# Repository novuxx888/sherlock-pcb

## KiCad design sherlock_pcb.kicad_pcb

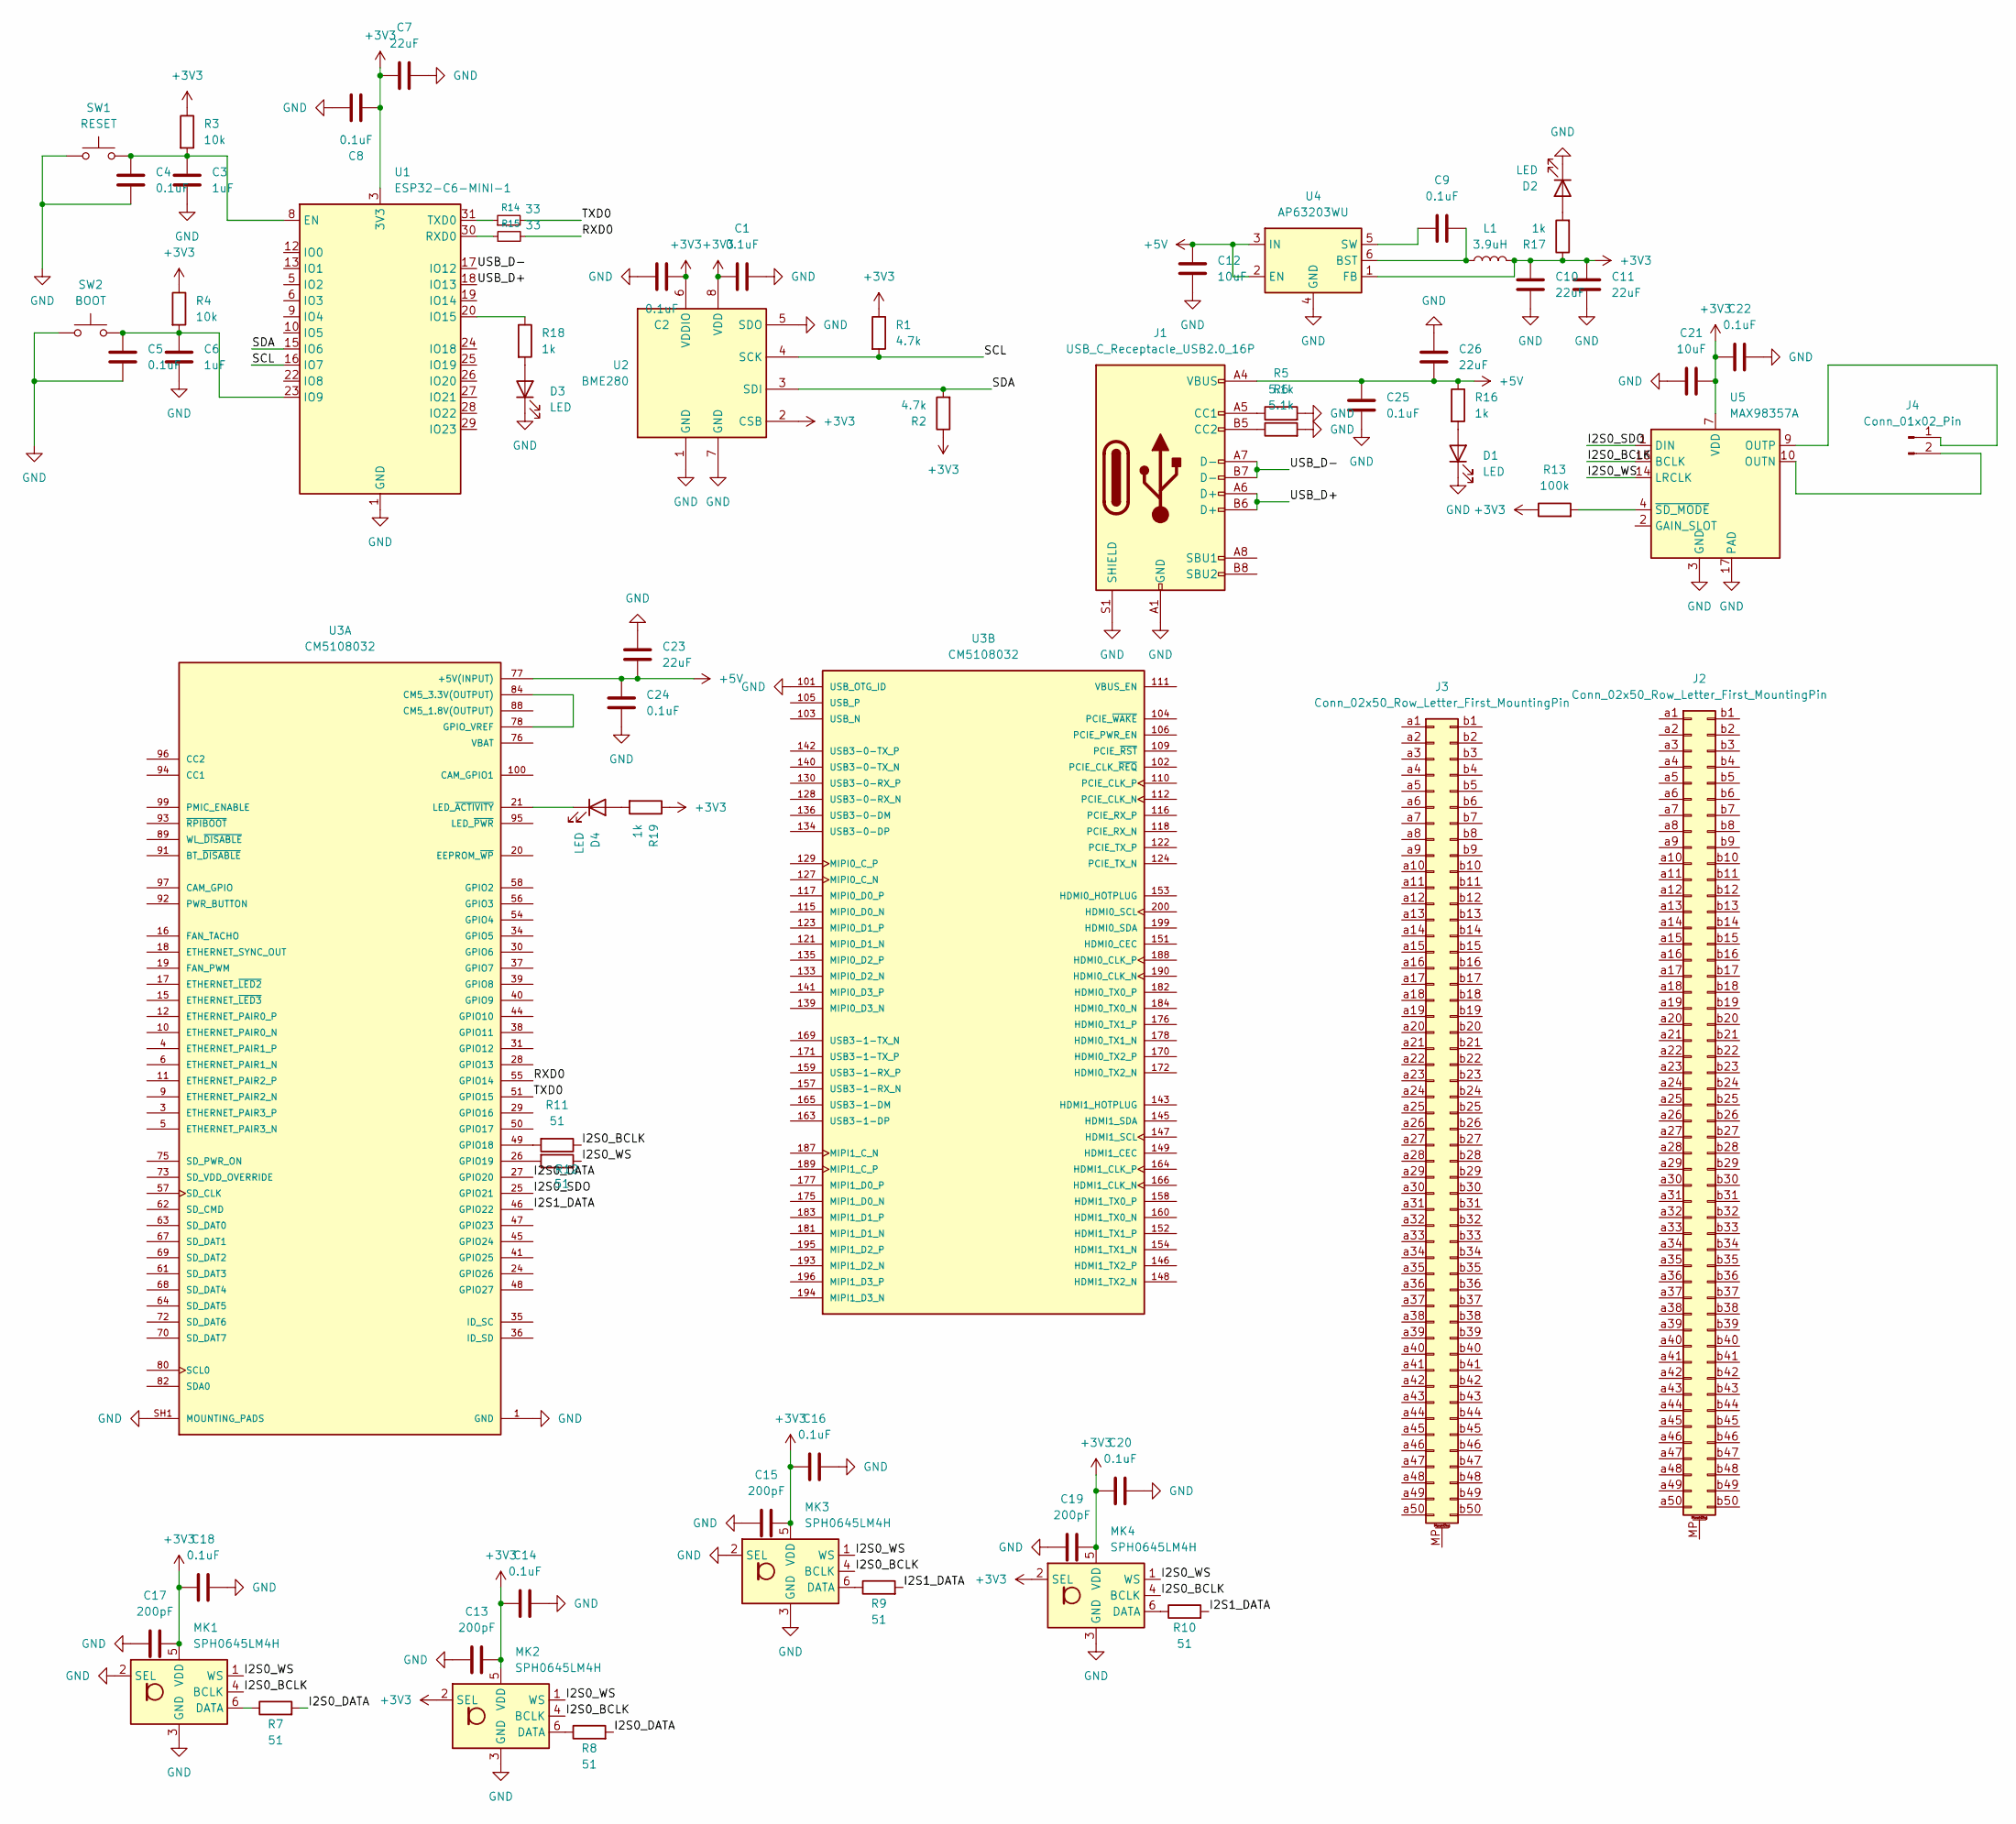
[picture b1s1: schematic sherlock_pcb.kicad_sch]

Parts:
C1, C2, C4, C5, C8, C9, C14, C16, C18, C20, C22, C24, C25: 0.1uF; C_0402_1005Metric; LCSC C1525
C3, C6: 1uF; C_0402_1005Metric; LCSC C52923
C7, C10, C11, C23, C26: 22uF; C_0603_1608Metric; LCSC C59461
C12, C21: 10uF; C_0603_1608Metric; LCSC C1691
C13, C15, C17, C19: 200pF; C_0402_1005Metric; LCSC C1529
D1, D2, D3, D4: LED; LED_0603_1608Metric; LCSC C2290
J1: USB_C_Receptacle_USB2.0_16P; USB_C_Receptacle_GCT_USB4105-xx-A_16P_TopMnt_Horizontal; LCSC C165948
J2, J3: Conn_02x50_Row_Letter_First_MountingPin; Hirose_DF40C-100DS-0.4V_2x50_P0.4mm; LCSC C597931
J4: Conn_01x02_Pin; Molex_PicoBlade_53261-0271_1x02-1MP_P1.25mm_Horizontal; LCSC C22074
L1: 3.9uH; L_1008_2520Metric; LCSC C250157
MK1, MK2, MK3, MK4: SPH0645LM4H; Knowles_SPH0645LM4H-6_3.5x2.65mm; LCSC C19272537
R1, R2: 4.7k; R_0402_1005Metric; LCSC C25900
R3, R4: 10k; R_0402_1005Metric; LCSC C25531
R5, R6: 5.1k; R_0402_1005Metric; LCSC C25905
R7, R8, R9, R10, R11, R12: 51; R_0402_1005Metric; LCSC C25125
R13: 100k; R_0402_1005Metric; LCSC C25530
R14, R15: 33; R_0402_1005Metric; LCSC C25105
R16, R17, R18, R19: 1k; R_0402_1005Metric; LCSC C11702
SW1: RESET; SW_SPST_PTS810; LCSC C221895
SW2: BOOT; SW_SPST_PTS810; LCSC C221895
U1: ESP32-C6-MINI-1; LCSC C5736265
U2: BME280; Bosch_LGA-8_2.5x2.5mm_P0.65mm_ClockwisePinNumbering; LCSC C92489
U3: CM5108032; MODULE_CM5108032; PARTREV 2024-11-27
U4: AP63203WU; TSOT-23-6; LCSC C2071056
U5: MAX98357A; TQFN-16-1EP_3x3mm_P0.5mm_EP1.23x1.23mm; LCSC C2682619

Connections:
+3V3: C1.1, C2.1, C7.2, C8.1, C10.2, C11.2, C13.2, C14.1, C15.2, C16.1, C17.2, C18.1, C19.2, C20.1, C21.1, C22.2, L1.2, MK1.5 (VDD), MK2.2 (SEL), MK2.5 (VDD), MK3.5 (VDD), MK4.2 (SEL), MK4.5 (VDD), R1.1, R2.1, R3.1, R4.1, R13.1, R17.1, R19.1, U1.3 (3V3), U2.2 (CSB), U2.6 (VDDIO), U2.8 (VDD), U4.1 (FB), U5.7 (VDD), U5.8 (VDD)
+5V: C12.2, C23.2, C24.2, C25.2, C26.2, J1.A4 (VBUS), J1.A9 (VBUS), J1.B4 (VBUS), J1.B9 (VBUS), R16.1, U3.77 (+5V(INPUT)), U3.79 (+5V(INPUT)), U3.81 (+5V(INPUT)), U3.83 (+5V(INPUT)), U3.85 (+5V(INPUT)), U3.87 (+5V(INPUT)), U4.2 (EN), U4.3 (IN)
/I2S0_BCLK: MK1.4 (BCLK), MK2.4 (BCLK), MK3.4 (BCLK), MK4.4 (BCLK), R11.1, U5.16 (BCLK)
/I2S0_DATA: R7.2, R8.2, U3.27 (GPIO20)
/I2S0_SDO: U3.25 (GPIO21), U5.1 (DIN)
/I2S0_WS: MK1.1 (WS), MK2.1 (WS), MK3.1 (WS), MK4.1 (WS), R12.1, U5.14 (LRCLK)
/I2S1_DATA: R9.2, R10.2, U3.46 (GPIO22)
/RXD0: R15.2, U3.55 (GPIO14)
/SCL: R1.2, U1.16 (IO7), U2.4 (SCK)
/SDA: R2.2, U1.15 (IO6), U2.3 (SDI)
/TXD0: R14.2, U3.51 (GPIO15)
/USB_D+: J1.A6 (D+), J1.B6 (D+), U1.18 (IO13)
/USB_D-: J1.A7 (D-), J1.B7 (D-), U1.17 (IO12)
CM5_1.8V(OUTPUT): U3.88 (CM5_1.8V(OUTPUT)), U3.90 (CM5_1.8V(OUTPUT))
CM5_3.3V(OUTPUT): U3.78 (GPIO_VREF), U3.84 (CM5_3.3V(OUTPUT)), U3.86 (CM5_3.3V(OUTPUT))
GND: C1.2, C2.2, C3.2, C4.2, C5.2, C6.2, C7.1, C8.2, C10.1, C11.1, C12.1, C13.1, C14.2, C15.1, C16.2, C17.1, C18.2, C19.1, C20.2, C21.2, C22.1, C23.1, C24.1, C25.1, C26.1, D1.1 (K), D2.1 (K), D3.1 (K), J1.A1 (GND), J1.A12 (GND), J1.B1 (GND), J1.B12 (GND), J1.S1 (SHIELD), MK1.2 (SEL), MK1.3 (GND), MK2.3 (GND), MK3.2 (SEL), MK3.3 (GND), MK4.3 (GND), R5.2, R6.2, SW1.1, SW2.1, U1.1 (GND), U1.2 (GND), U1.11 (GND), U1.14 (GND), U1.36 (GND), U1.37 (GND), U1.38 (GND), U1.39 (GND), U1.40 (GND), U1.41 (GND), U1.42 (GND), U1.43 (GND), U1.44 (GND), U1.45 (GND), U1.46 (GND), U1.47 (GND), U1.48 (GND), U1.49 (GND), U1.50 (GND), U1.51 (GND), U1.52 (GND), U1.53 (GND), U2.1 (GND), U2.5 (SDO), U2.7 (GND), U3.1 (GND), U3.2 (GND), U3.7 (GND), U3.8 (GND), U3.13 (GND), U3.14 (GND), U3.22 (GND), U3.23 (GND), U3.32 (GND), U3.33 (GND), U3.42 (GND), U3.43 (GND), U3.52 (GND), U3.53 (GND), U3.59 (GND), U3.60 (GND), U3.65 (GND), U3.66 (GND), U3.71 (GND), U3.74 (GND), U3.98 (GND), U3.101 (USB_OTG_ID), U3.107 (GND), U3.108 (GND), U3.113 (GND), U3.114 (GND), U3.119 (GND), U3.120 (GND), U3.125 (GND), U3.126 (GND), U3.131 (GND), U3.132 (GND), U3.137 (GND), U3.138 (GND), U3.144 (GND), U3.150 (GND), U3.155 (GND), U3.156 (GND), U3.161 (GND), U3.162 (GND), U3.167 (GND), U3.168 (GND), U3.173 (GND), U3.174 (GND), U3.179 (GND), U3.180 (GND), U3.185 (GND), U3.186 (GND), U3.191 (GND), U3.192 (GND), U3.197 (GND), U3.198 (GND), U3.SH1 (MOUNTING_PADS), U3.SH2 (MOUNTING_PADS), U3.SH3 (MOUNTING_PADS), U3.SH4 (MOUNTING_PADS), U4.4 (GND), U5.3 (GND), U5.11 (GND), U5.15 (GND), U5.17 (PAD)
unnamed: D1.2 (A), R16.2
unnamed: D2.2 (A), R17.2
unnamed: D3.2 (A), R18.2
unnamed: D4.2 (A), R19.2
unnamed: D4.1 (K), U3.21 (LED_~ACTIVITY)
unnamed: J1.A5 (CC1), R5.1
unnamed: J1.B5 (CC2), R6.1
unnamed: J4.1, U5.9 (OUTP)
unnamed: J4.2, U5.10 (OUTN)
unnamed: MK1.6 (DATA), R7.1
unnamed: MK2.6 (DATA), R8.1
unnamed: MK3.6 (DATA), R9.1
unnamed: MK4.6 (DATA), R10.1
unnamed: C3.1, C4.1, R3.2, SW1.2, U1.8 (EN)
unnamed: C5.1, C6.1, R4.2, SW2.2, U1.23 (IO9)
unnamed: R18.1, U1.20 (IO15)
unnamed: R15.1, U1.30 (RXD0)
unnamed: R14.1, U1.31 (TXD0)
unnamed: R11.2, U3.49 (GPIO18)
unnamed: R12.2, U3.26 (GPIO19)
unnamed: C9.2, L1.1, U4.6 (BST)
unnamed: C9.1, U4.5 (SW)
unnamed: R13.2, U5.4 (~SD_MODE)

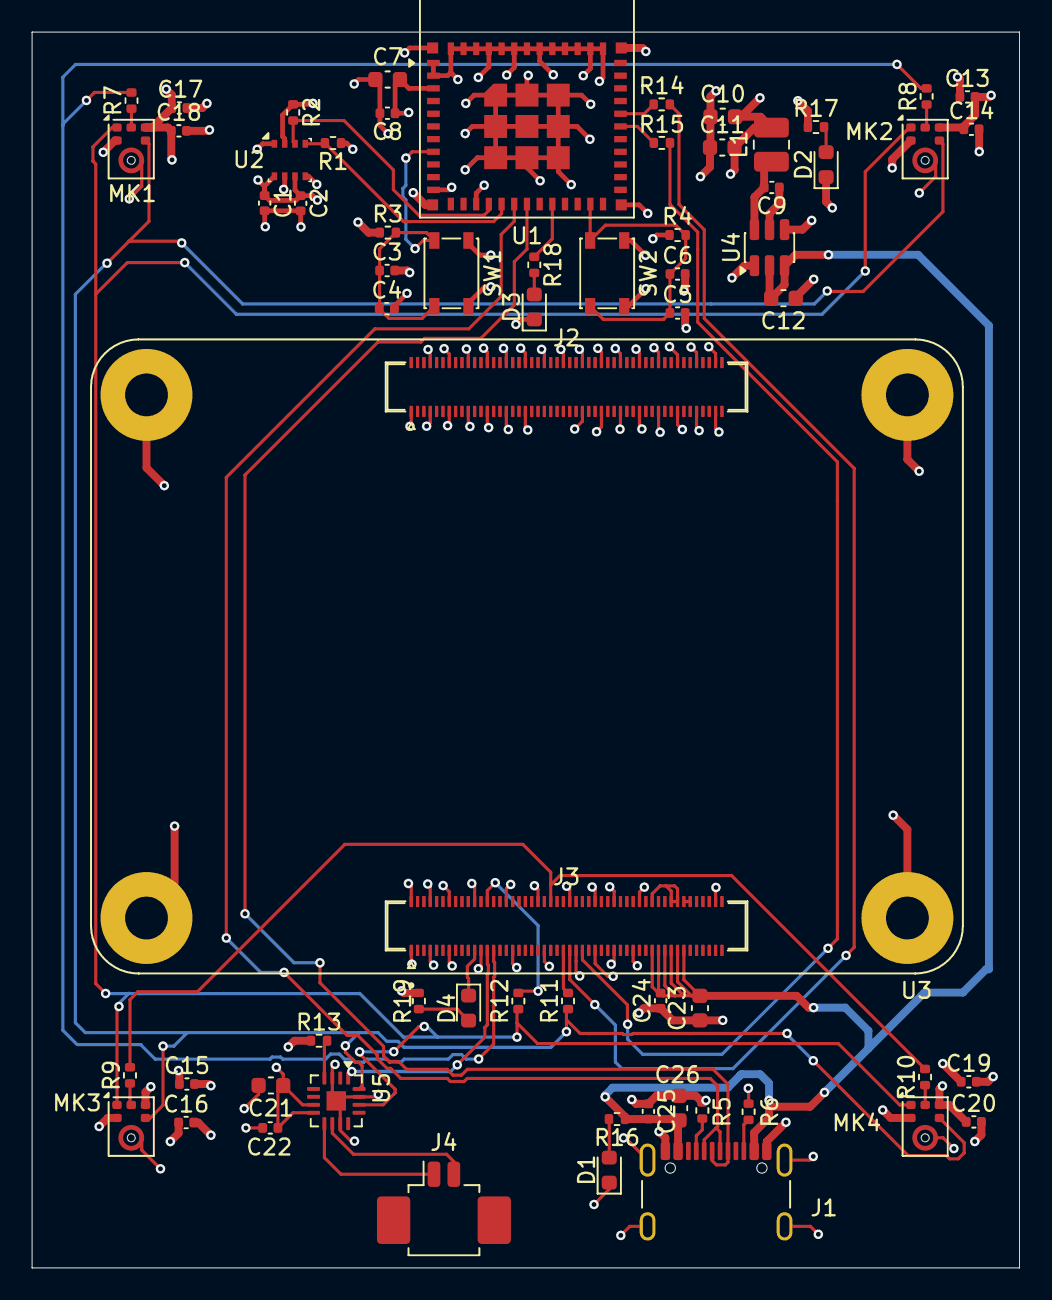
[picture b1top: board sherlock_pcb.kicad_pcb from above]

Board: 4 copper layers, 62.3 x 78.0 mm, 65 parts (0 on the bottom side), 39 nets.

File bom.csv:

Designator,Footprint,Quantity,Value,LCSC Part #
"C1, C14, C16, C18, C2, C20, C22, C24, C25, C4, C5, C8, C9",0402,13,0.1uF,C1525
"C10, C11, C23, C26, C7",0603,5,22uF,C59461
"C12, C21",0603,2,10uF,C1691
"C13, C15, C17, C19",0402,4,200pF,C1529
"C3, C6",0402,2,1uF,C52923
"D1, D2, D3, D4",0603,4,LED,C2290
J1,USB_C_Receptacle_GCT_USB4105-xx-A_16P_TopMnt_Horizontal,1,USB_C_Receptacle_USB2.0_16P,C165948
"J2, J3",Hirose_DF40C-100DS-0.4V_2x50_P0.4mm,2,Conn_02x50_Row_Letter_First_MountingPin,C597931
J4,Molex_PicoBlade_53261-0271_1x02-1MP_P1.25mm_Horizontal,1,Conn_01x02_Pin,C22074
L1,1008,1,3.9uH,C250157
"MK1, MK2, MK3, MK4",Knowles_SPH0645LM4H-6_3.5x2.65mm,4,SPH0645LM4H,C19272537
"R1, R2",0402,2,4.7k,C25900
"R10, R11, R12, R7, R8, R9",0402,6,51,C25125
R13,0402,1,100k,C25530
"R14, R15",0402,2,33,C25105
"R16, R17, R18, R19",0402,4,1k,C11702
"R3, R4",0402,2,10k,C25531
"R5, R6",0402,2,5.1k,C25905
SW1,SW_SPST_PTS810,1,RESET,C221895
SW2,SW_SPST_PTS810,1,BOOT,C221895
U1,ESP32-C6-MINI-1,1,ESP32-C6-MINI-1,C5736265
U2,Bosch_LGA-8_2.5x2.5mm_P0.65mm_ClockwisePinNumbering,1,BME280,C92489
U4,TSOT-23-6,1,AP63203WU,C2071056
U5,TQFN-16-1EP_3x3mm_P0.5mm_EP1.23x1.23mm,1,MAX98357A,C2682619

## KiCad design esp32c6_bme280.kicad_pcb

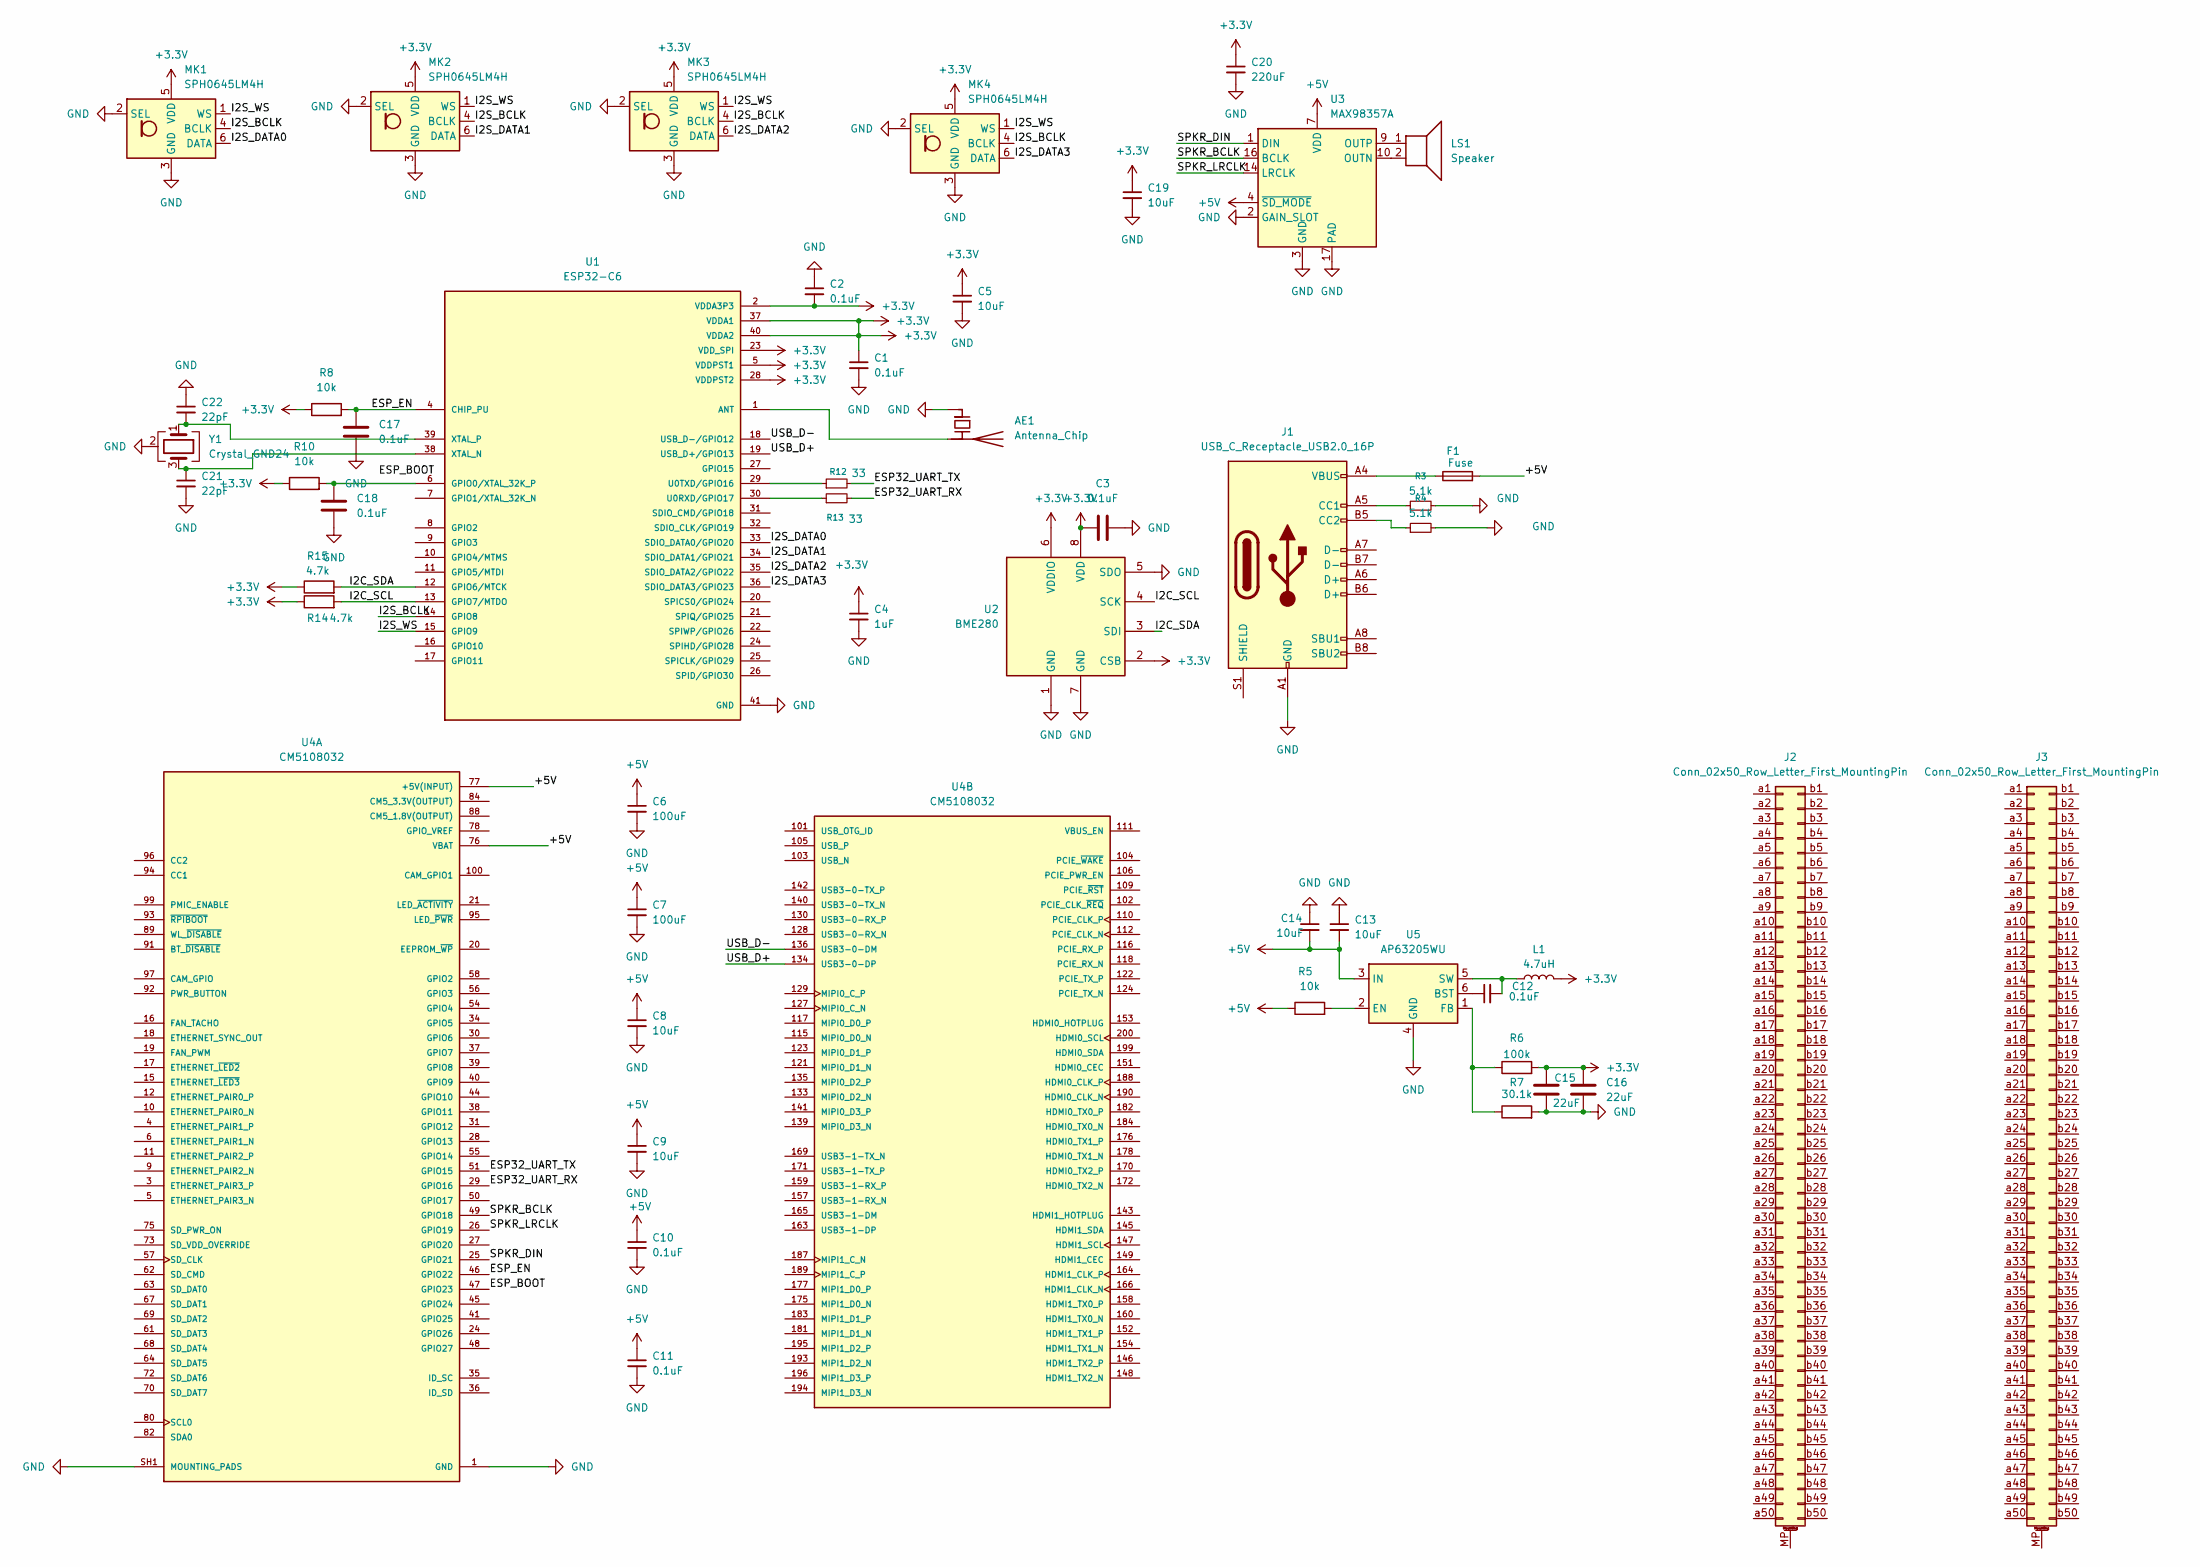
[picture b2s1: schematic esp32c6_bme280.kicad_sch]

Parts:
AE1: Antenna_Chip; Johanson_2450AT18x100; LCSC C89334
C1, C2, C3, C10, C11, C12, C17, C18: 0.1uF; C_0402_1005Metric; LCSC C1525
C4: 1uF; C_0402_1005Metric; LCSC C52923
C5, C8, C9, C13, C14, C19: 10uF; C_0402_1005Metric; LCSC C15525
C6, C7: 100uF; C_0805_2012Metric; LCSC C141660
C15, C16: 22uF; C_0603_1608Metric; LCSC C109448
C20: 220uF; C_1206_3216Metric; LCSC C412252
C21, C22: 22pF; C_0603_1608Metric; LCSC C1653
F1: Fuse; Fuse_1206_3216Metric; LCSC C883135
J1: USB_C_Receptacle_USB2.0_16P; USB_C_Receptacle_GCT_USB4105-xx-A_16P_TopMnt_Horizontal; LCSC C165948
J2, J3: Conn_02x50_Row_Letter_First_MountingPin; Hirose_DF40C-100DS-0.4V_2x50_P0.4mm; LCSC C597931
L1: 4.7uH; L_0805_2012Metric; LCSC C63166
LS1: Speaker; PinHeader_1x02_P2.54mm_Vertical
MK1, MK2, MK3, MK4: SPH0645LM4H; Knowles_SPH0645LM4H-6_3.5x2.65mm; LCSC C19272537
R3, R4: 5.1k; R_0603_1608Metric_Pad0.98x0.95mm_HandSolder; LCSC C23186
R5, R8, R10: 10k; R_0603_1608Metric_Pad0.98x0.95mm_HandSolder; LCSC C25804
R6: 100k; R_0603_1608Metric_Pad0.98x0.95mm_HandSolder; LCSC C25803
R7: 30.1k; R_0603_1608Metric_Pad0.98x0.95mm_HandSolder; LCSC C137745
R12, R13: 33; R_0603_1608Metric_Pad0.98x0.95mm_HandSolder; LCSC C23140
R14, R15: 4.7k; R_0603_1608Metric_Pad0.98x0.95mm_HandSolder; LCSC C23162
U1: ESP32-C6; QFN40P500X500X90-41N; PARTREV v0.5; LCSC C5364646
U2: BME280; Bosch_LGA-8_2.5x2.5mm_P0.65mm_ClockwisePinNumbering; LCSC C92489
U3: MAX98357A; TQFN-16-1EP_3x3mm_P0.5mm_EP1.23x1.23mm; LCSC C2682619
U4: CM5108032; MODULE_CM5108032; PARTREV 2024-11-27
U5: AP63205WU; TSOT-23-6; LCSC C2071056
Y1: Crystal_GND24; Crystal_SMD_3225-4Pin_3.2x2.5mm; LCSC C9010

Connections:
+3.3V: C1.1, C2.2, C3.1, C4.1, C5.1, C15.1, C16.1, C19.1, C20.1, L1.2, MK1.5 (VDD), MK2.5 (VDD), MK3.5 (VDD), MK4.5 (VDD), R6.2, R8.1, R10.1, R14.1, R15.1, U1.2 (VDDA3P3), U1.3 (VDDA3P3), U1.5 (VDDPST1), U1.23 (VDD_SPI), U1.28 (VDDPST2), U1.37 (VDDA1), U1.40 (VDDA2), U2.2 (CSB), U2.6 (VDDIO), U2.8 (VDD)
+5V: C6.1, C7.1, C8.1, C9.1, C10.1, C11.1, C13.2, C14.2, F1.2, R5.1, U3.4 (~SD_MODE), U3.7 (VDD), U3.8 (VDD), U4.76 (VBAT), U4.77 (+5V(INPUT)), U4.79 (+5V(INPUT)), U4.81 (+5V(INPUT)), U4.83 (+5V(INPUT)), U4.85 (+5V(INPUT)), U4.87 (+5V(INPUT)), U5.3 (IN)
/ESP32_UART_RX: R13.2, U4.29 (GPIO16)
/ESP32_UART_TX: R12.2, U4.51 (GPIO15)
/ESP_BOOT: U4.47 (GPIO23)
/ESP_EN: C17.1, R8.2, U1.4 (CHIP_PU), U4.46 (GPIO22)
/I2C_SCL: R14.2, U1.13 (GPIO7/MTDO), U2.4 (SCK)
/I2C_SDA: R15.2, U1.12 (GPIO6/MTCK), U2.3 (SDI)
/I2S_BCLK: MK1.4 (BCLK), MK2.4 (BCLK), MK3.4 (BCLK), MK4.4 (BCLK), U1.14 (GPIO8)
/I2S_DATA0: MK1.6 (DATA), U1.33 (SDIO_DATA0/GPIO20)
/I2S_DATA1: MK2.6 (DATA), U1.34 (SDIO_DATA1/GPIO21)
/I2S_DATA2: MK3.6 (DATA), U1.35 (SDIO_DATA2/GPIO22)
/I2S_DATA3: MK4.6 (DATA), U1.36 (SDIO_DATA3/GPIO23)
/I2S_WS: MK1.1 (WS), MK2.1 (WS), MK3.1 (WS), MK4.1 (WS), U1.15 (GPIO9)
/SPKR_BCLK: U3.16 (BCLK), U4.49 (GPIO18)
/SPKR_DIN: U3.1 (DIN), U4.25 (GPIO21)
/SPKR_LRCLK: U3.14 (LRCLK), U4.26 (GPIO19)
/USB_D+: U1.19 (USB_D+/GPIO13), U4.134 (USB3-0-DP)
/USB_D-: U1.18 (USB_D-/GPIO12), U4.136 (USB3-0-DM)
CM5_1.8V(OUTPUT): U4.88 (CM5_1.8V(OUTPUT)), U4.90 (CM5_1.8V(OUTPUT))
CM5_3.3V(OUTPUT): U4.84 (CM5_3.3V(OUTPUT)), U4.86 (CM5_3.3V(OUTPUT))
unnamed: AE1.2 (PCB_Trace), U1.1 (ANT)
unnamed: F1.1, J1.A4 (VBUS), J1.A9 (VBUS), J1.B4 (VBUS), J1.B9 (VBUS)
unnamed: J1.A5 (CC1), R3.1
unnamed: J1.B5 (CC2), R4.1
unnamed: C18.1, R10.2, U1.6 (GPIO0/XTAL_32K_P)
unnamed: R13.1, U1.30 (U0RXD/GPIO17)
unnamed: R12.1, U1.29 (U0TXD/GPIO16)
unnamed: C22.2, U1.39 (XTAL_P), Y1.1
unnamed: LS1.2, U3.10 (OUTN)
unnamed: LS1.1, U3.9 (OUTP)
unnamed: C12.1, U5.6 (BST)
unnamed: R5.2, U5.2 (EN)
unnamed: R6.1, R7.1, U5.1 (FB)
unnamed: C12.2, L1.1, U5.5 (SW)

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
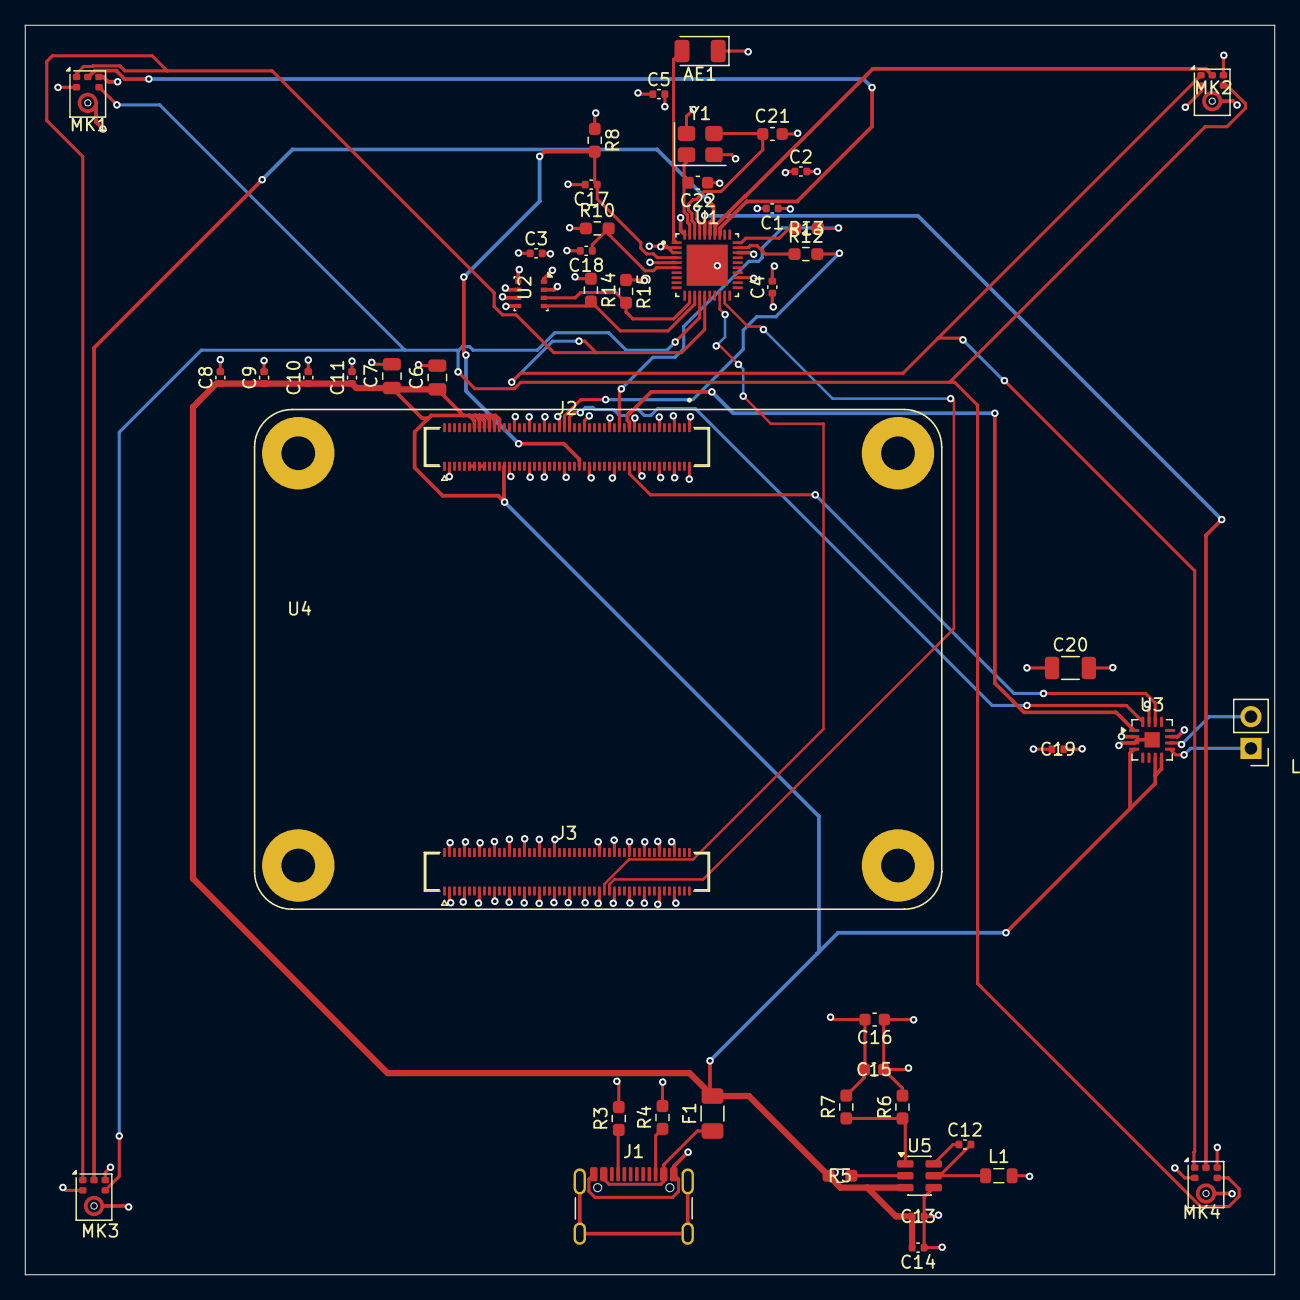
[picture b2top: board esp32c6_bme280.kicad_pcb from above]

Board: 4 copper layers, 100.0 x 100.0 mm, 50 parts (0 on the bottom side), 36 nets.
